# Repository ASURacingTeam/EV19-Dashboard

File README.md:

# ASU Racing Team Formula Students Electric 2019 Dashboard

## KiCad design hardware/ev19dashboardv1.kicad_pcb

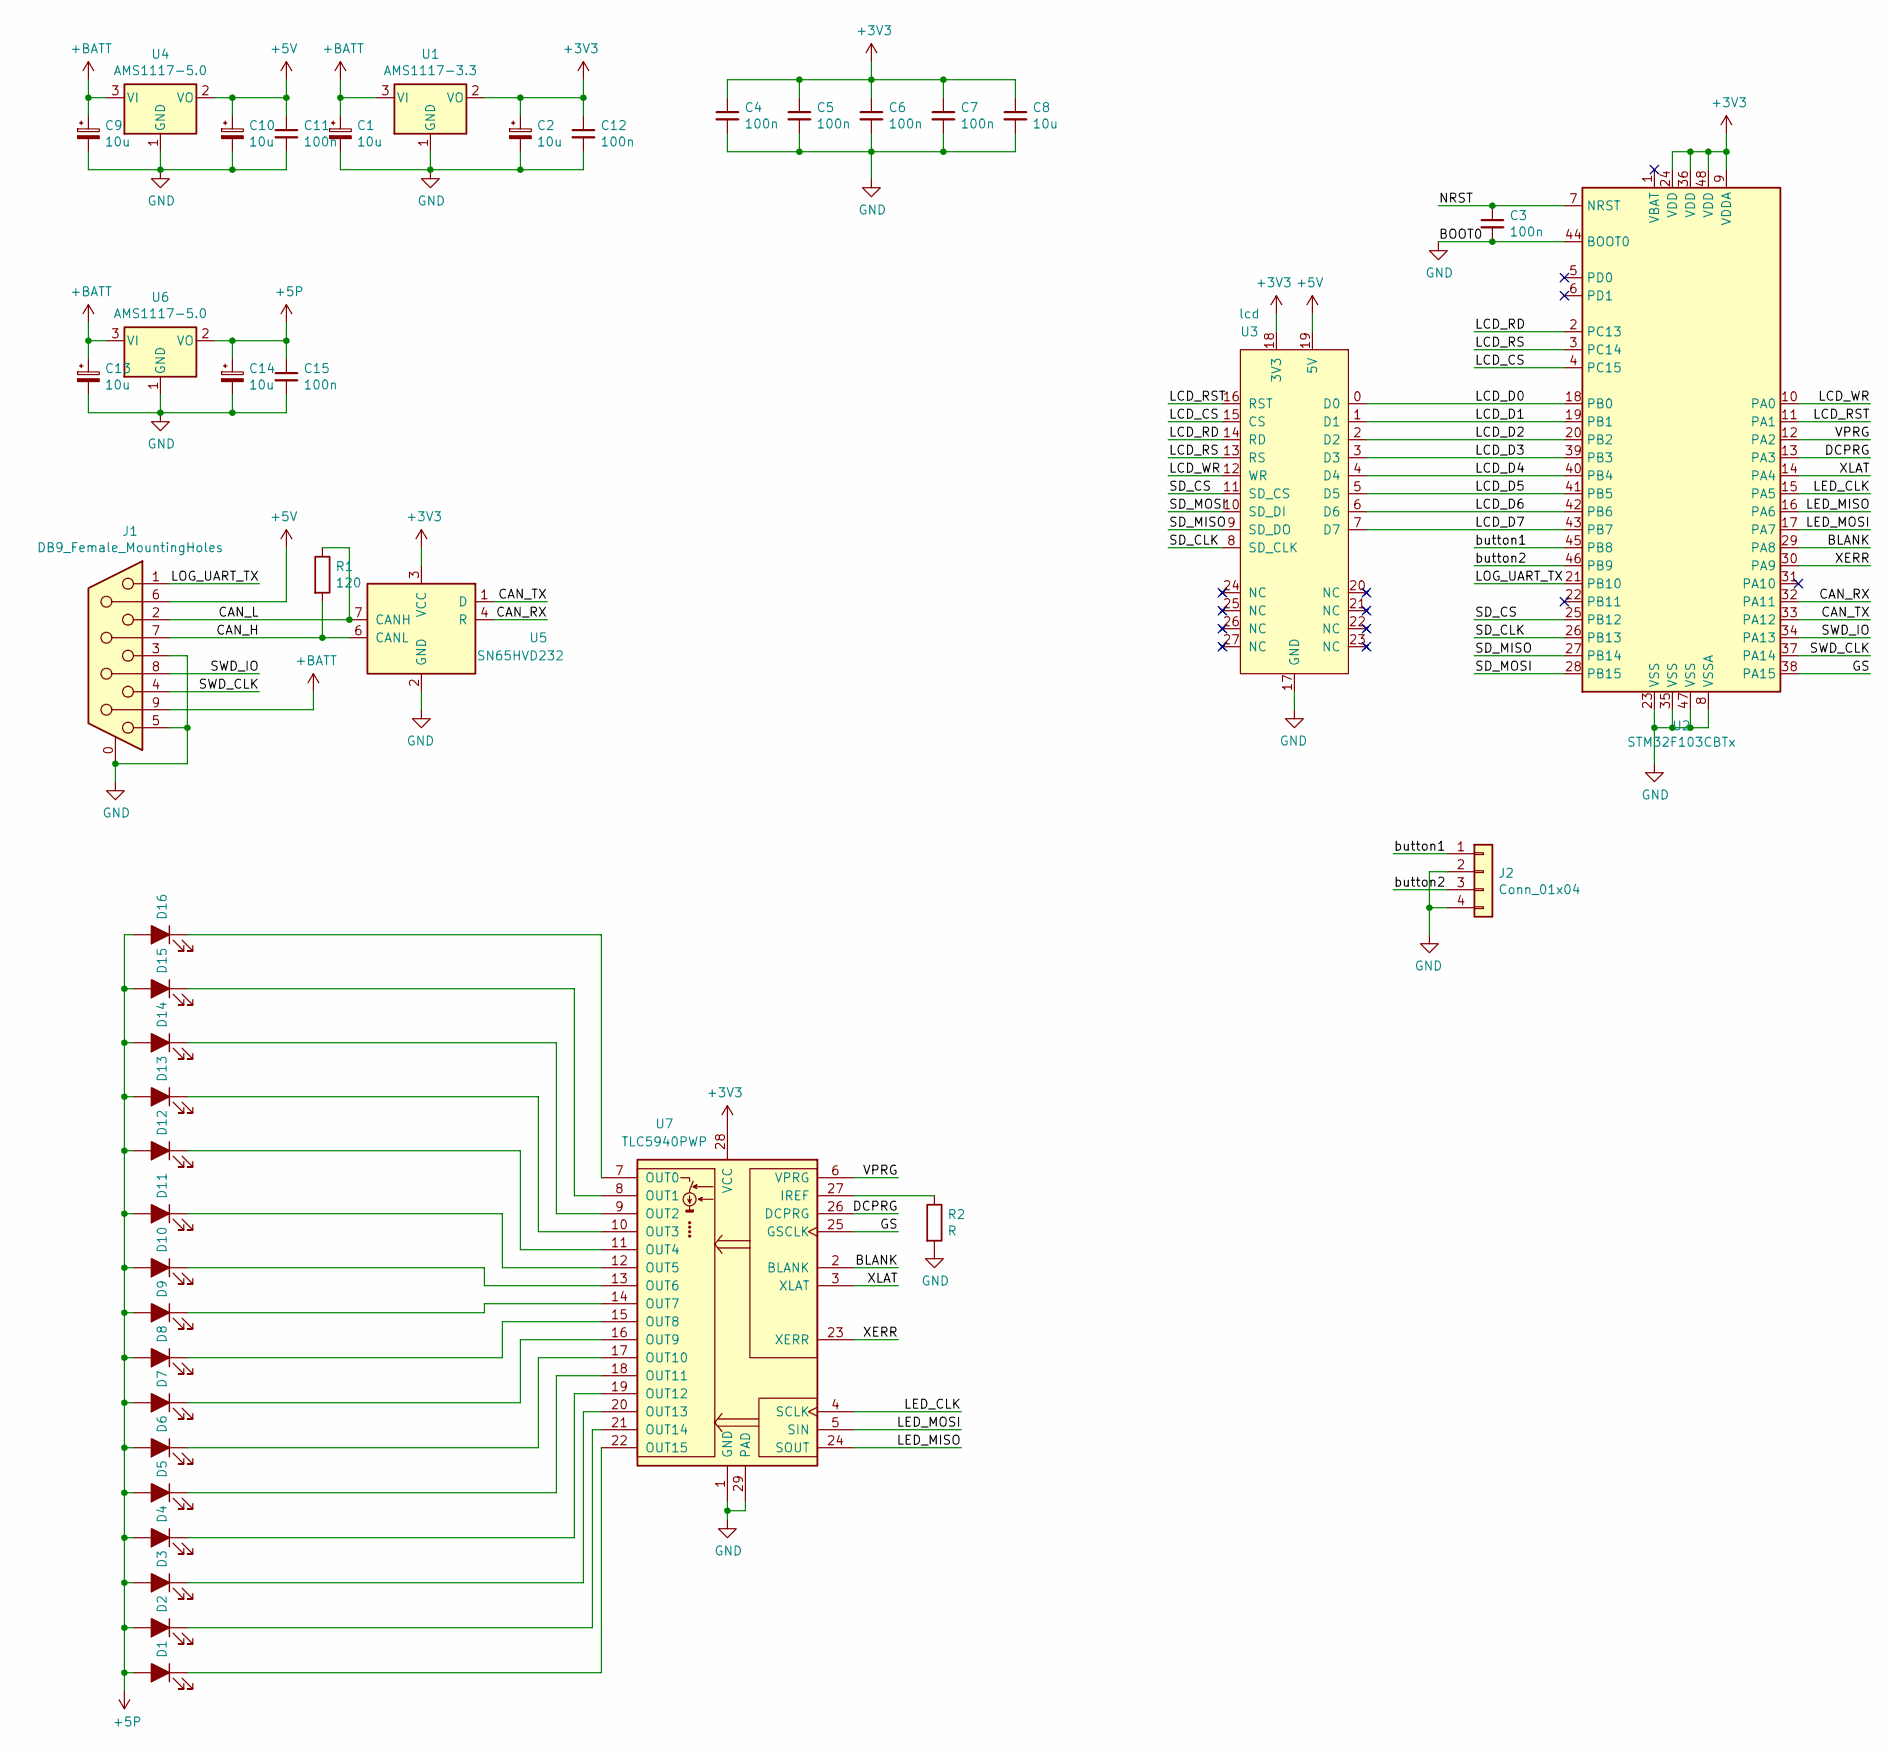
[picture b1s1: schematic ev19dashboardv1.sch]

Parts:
C1, C2, C8, C9, C10, C13, C14: 10u; C_1206_3216Metric_Pad1.42x1.75mm_HandSolder
C3, C4, C5, C6, C7, C11, C12, C15: 100n; C_0805_2012Metric_Pad1.15x1.40mm_HandSolder
D1, D2, D3, D4, D5, D6, D7, D8, D9, D10, D11, D12, D13, D14, D15, D16: LED_ALT; LED_D5.0mm
J1: DB9_Female_MountingHoles; DSUB-9_Female_Vertical_P2.77x2.84mm_MountingHoles
J2: Conn_01x04; PinHeader_1x04_P2.54mm_Vertical
R1: 120; R_0805_2012Metric_Pad1.15x1.40mm_HandSolder
R2: R; R_0805_2012Metric_Pad1.15x1.40mm_HandSolder
U1: AMS1117-3.3; SOT-223-3_TabPin2
U2: STM32F103CBTx; LQFP-48_7x7mm_P0.5mm
U3: lcd; Arduino_35_LCD
U4, U6: AMS1117-5.0; SOT-223-3_TabPin2
U5: SN65HVD232; SOIC-8_3.9x4.9mm_P1.27mm
U7: TLC5940PWP; HTSSOP-28-1EP_4.4x9.7mm_P0.65mm_EP3.4x9.5mm_Mask2.4x6.17mm_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

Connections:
+3V3: C2.1, C4.1, C5.1, C6.1, C7.1, C8.1, C12.1, U1.2 (VO), U2.9 (VDDA), U2.24 (VDD), U2.36 (VDD), U2.48 (VDD), U3.18 (3V3), U5.3 (VCC), U7.28 (VCC)
+5P: C14.1, C15.1, D1.2 (A), D2.2 (A), D3.2 (A), D4.2 (A), D5.2 (A), D6.2 (A), D7.2 (A), D8.2 (A), D9.2 (A), D10.2 (A), D11.2 (A), D12.2 (A), D13.2 (A), D14.2 (A), D15.2 (A), D16.2 (A), U6.2 (VO)
+5V: C10.1, C11.1, J1.6, U3.19 (5V), U4.2 (VO)
+BATT: C1.1, C9.1, C13.1, J1.9, U1.3 (VI), U4.3 (VI), U6.3 (VI)
/BLANK: U2.29 (PA8), U7.2 (BLANK)
/CAN_H: J1.7, R1.2, U5.6 (CANL)
/CAN_L: J1.2, R1.1, U5.7 (CANH)
/CAN_RX: U2.32 (PA11), U5.4 (R)
/CAN_TX: U2.33 (PA12), U5.1 (D)
/DCPRG: U2.13 (PA3), U7.26 (DCPRG)
/GS: U2.38 (PA15), U7.25 (GSCLK)
/LCD_CS: U2.4 (PC15), U3.15 (CS)
/LCD_D0: U2.18 (PB0), U3.0 (D0)
/LCD_D1: U2.19 (PB1), U3.1 (D1)
/LCD_D2: U2.20 (PB2), U3.2 (D2)
/LCD_D3: U2.39 (PB3), U3.3 (D3)
/LCD_D4: U2.40 (PB4), U3.4 (D4)
/LCD_D5: U2.41 (PB5), U3.5 (D5)
/LCD_D6: U2.42 (PB6), U3.6 (D6)
/LCD_D7: U2.43 (PB7), U3.7 (D7)
/LCD_RD: U2.2 (PC13), U3.14 (RD)
/LCD_RS: U2.3 (PC14), U3.13 (RS)
/LCD_RST: U2.11 (PA1), U3.16 (RST)
/LCD_WR: U2.10 (PA0), U3.12 (WR)
/LED_CLK: U2.15 (PA5), U7.4 (SCLK)
/LED_MISO: U2.16 (PA6), U7.24 (SOUT)
/LED_MOSI: U2.17 (PA7), U7.5 (SIN)
/LOG_UART_TX: J1.1, U2.21 (PB10)
/NRST: C3.1, U2.7 (NRST)
/SD_CLK: U2.26 (PB13), U3.8 (SD_CLK)
/SD_CS: U2.25 (PB12), U3.11 (SD_CS)
/SD_MISO: U2.27 (PB14), U3.9 (SD_DO)
/SD_MOSI: U2.28 (PB15), U3.10 (SD_DI)
/SWD_CLK: J1.4, U2.37 (PA14)
/SWD_IO: J1.8, U2.34 (PA13)
/VPRG: U2.12 (PA2), U7.6 (VPRG)
/XERR: U2.30 (PA9), U7.23 (XERR)
/XLAT: U2.14 (PA4), U7.3 (XLAT)
/button1: J2.1, U2.45 (PB8)
/button2: J2.3, U2.46 (PB9)
GND: C1.2, C2.2, C3.2, C4.2, C5.2, C6.2, C7.2, C8.2, C9.2, C10.2, C11.2, C12.2, C13.2, C14.2, C15.2, J1.0 (PAD), J1.3, J1.5, J2.2, J2.4, R2.2, U1.1 (GND), U2.8 (VSSA), U2.23 (VSS), U2.35 (VSS), U2.44 (BOOT0), U2.47 (VSS), U3.17 (GND), U4.1 (GND), U5.2 (GND), U6.1 (GND), U7.1 (GND), U7.29 (PAD)
unnamed: D1.1 (K), U7.22 (OUT15)
unnamed: D2.1 (K), U7.21 (OUT14)
unnamed: D3.1 (K), U7.20 (OUT13)
unnamed: D4.1 (K), U7.19 (OUT12)
unnamed: D5.1 (K), U7.18 (OUT11)
unnamed: D6.1 (K), U7.17 (OUT10)
unnamed: D7.1 (K), U7.16 (OUT9)
unnamed: D8.1 (K), U7.15 (OUT8)
unnamed: D9.1 (K), U7.14 (OUT7)
unnamed: D10.1 (K), U7.13 (OUT6)
unnamed: D11.1 (K), U7.12 (OUT5)
unnamed: D12.1 (K), U7.11 (OUT4)
unnamed: D13.1 (K), U7.10 (OUT3)
unnamed: D14.1 (K), U7.9 (OUT2)
unnamed: D15.1 (K), U7.8 (OUT1)
unnamed: D16.1 (K), U7.7 (OUT0)
unnamed: R2.1, U7.27 (IREF)

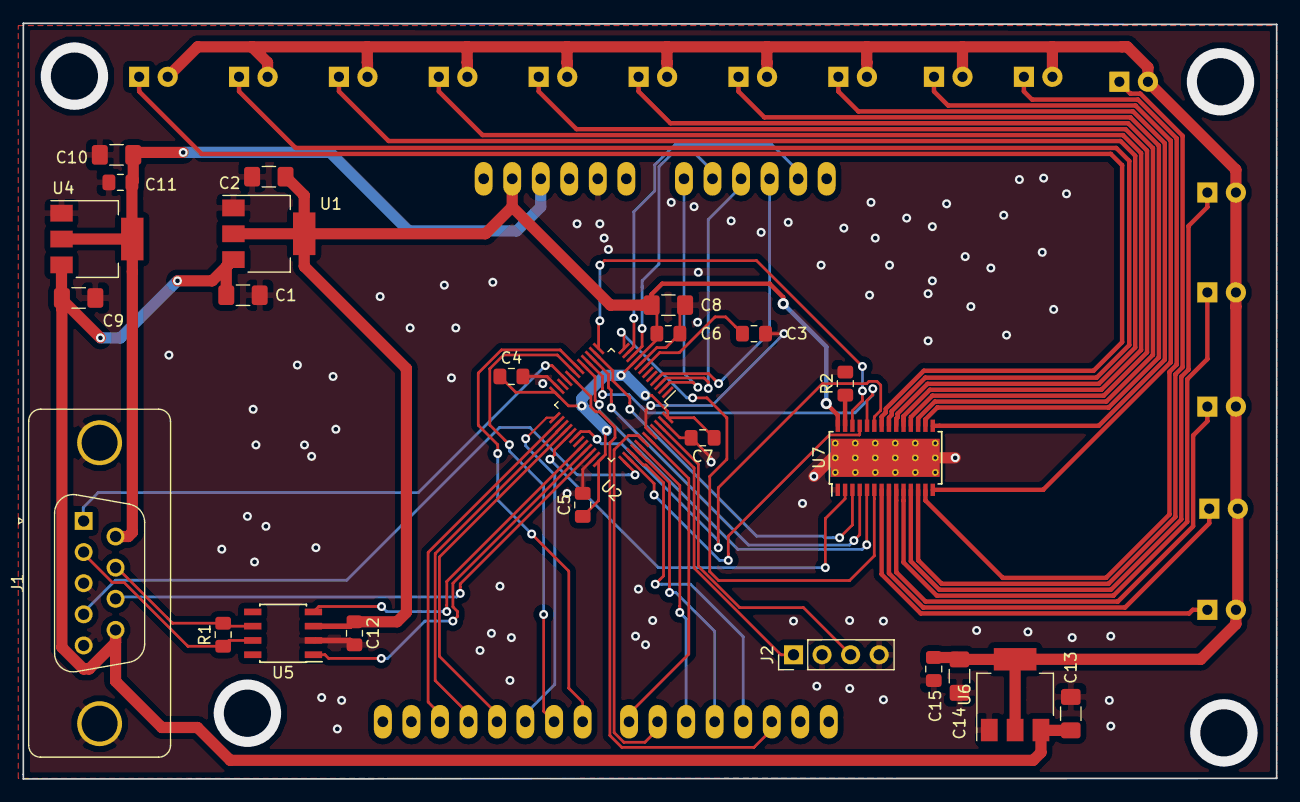
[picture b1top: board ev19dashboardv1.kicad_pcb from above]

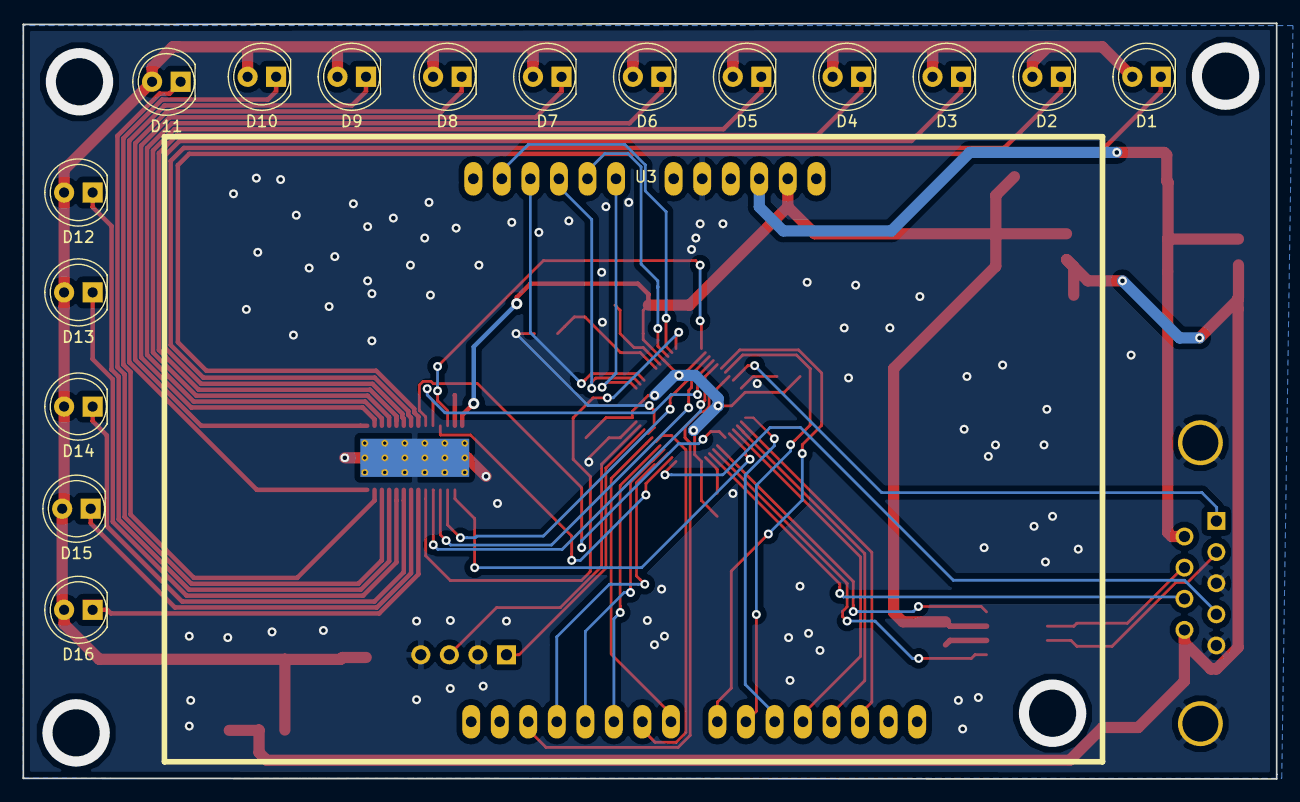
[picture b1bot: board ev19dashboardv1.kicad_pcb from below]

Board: 2 copper layers, 111.5 x 67.2 mm, 42 parts (17 on the bottom side), 58 nets.

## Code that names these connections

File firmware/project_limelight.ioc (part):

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Mcu.Name=STM32F103C(8-B)Tx
Mcu.Package=LQFP48
Mcu.UserName=STM32F103CBTx
PA0-WKUP.GPIOParameters=GPIO_Label
PA0-WKUP.GPIO_Label=LCD_WR
PA0-WKUP.Signal=GPIO_Output
PA1.GPIOParameters=GPIO_Label
PA1.GPIO_Label=LCD_RST
PA1.Signal=GPIO_Output
PA11.Mode=Master
PA11.Signal=CAN_RX
PA12.Mode=Master
PA12.Signal=CAN_TX
PA13.GPIOParameters=GPIO_Label
PA13.GPIO_Label=SWDIO
PA13.Mode=Serial_Wire
PA13.Signal=SYS_JTMS-SWDIO
PA14.GPIOParameters=GPIO_Label
PA14.GPIO_Label=SWCLK
PA14.Mode=Serial_Wire
PA14.Signal=SYS_JTCK-SWCLK
PA15.GPIOParameters=GPIO_Label
PA15.GPIO_Label=LED_GS
PA15.Signal=S_TIM2_CH1_ETR
PA2.GPIOParameters=GPIO_Label
PA2.GPIO_Label=LED_VPRG
PA2.Signal=GPIO_Output
PA3.GPIOParameters=GPIO_Label
PA3.GPIO_Label=LED_DCPRG
PA3.Signal=GPIO_Output
PA4.GPIOParameters=GPIO_Label
PA4.GPIO_Label=LED_XLAT
PA4.Signal=GPIO_Output
PA5.GPIOParameters=GPIO_Label
PA5.GPIO_Label=LED_CLK
PA5.Mode=Full_Duplex_Master
PA5.Signal=SPI1_SCK
PA6.GPIOParameters=GPIO_Label
PA6.GPIO_Label=LED_MISO
PA6.Mode=Full_Duplex_Master
PA6.Signal=SPI1_MISO
PA7.GPIOParameters=GPIO_Label
PA7.GPIO_Label=LED_MOSI
PA7.Mode=Full_Duplex_Master
PA7.Signal=SPI1_MOSI
PA8.GPIOParameters=PinState,GPIO_Label
PA8.GPIO_Label=LED_BLANK
PA8.PinState=GPIO_PIN_SET
PA8.Signal=GPIO_Output
PA9.GPIOParameters=GPIO_Label
PA9.GPIO_Label=LED_XERR
PA9.Signal=GPIO_Input
PB0.GPIOParameters=GPIO_Speed,PinState,GPIO_Label
PB0.GPIO_Label=LCD_D0
PB0.GPIO_Speed=GPIO_SPEED_FREQ_HIGH
PB0.PinState=GPIO_PIN_RESET
PB0.Signal=GPIO_Output
PB1.GPIOParameters=GPIO_Speed,GPIO_Label
PB1.GPIO_Label=LCD_D1
PB1.GPIO_Speed=GPIO_SPEED_FREQ_HIGH
PB1.Signal=GPIO_Output
PB10.GPIOParameters=GPIO_Label
PB10.GPIO_Label=LOG_UART_TX
PB10.Mode=Asynchronous
PB10.Signal=USART3_TX
PB11.GPIOParameters=GPIO_Label
PB11.GPIO_Label=UNUSED
PB11.Mode=Asynchronous
PB11.Signal=USART3_RX
PB12.GPIOParameters=GPIO_Label
PB12.GPIO_Label=SD_CS
PB12.Signal=GPIO_Output
PB13.GPIOParameters=GPIO_Label
PB13.GPIO_Label=SD_CLK
PB13.Mode=Full_Duplex_Master
PB13.Signal=SPI2_SCK
PB14.GPIOParameters=GPIO_PuPd,GPIO_Label
PB14.GPIO_Label=SD_MISO
PB14.GPIO_PuPd=GPIO_PULLUP
PB14.Mode=Full_Duplex_Master
PB14.Signal=SPI2_MISO
PB15.GPIOParameters=GPIO_Label
PB15.GPIO_Label=SD_MOSI
PB15.Mode=Full_Duplex_Master
PB15.Signal=SPI2_MOSI
PB2.GPIOParameters=GPIO_Speed,GPIO_Label
PB2.GPIO_Label=LCD_D2
PB2.GPIO_Speed=GPIO_SPEED_FREQ_HIGH
PB2.Signal=GPIO_Output
PB3.GPIOParameters=GPIO_Speed,GPIO_Label
PB3.GPIO_Label=LCD_D3
PB3.GPIO_Speed=GPIO_SPEED_FREQ_HIGH
PB3.Signal=GPIO_Output
PB4.GPIOParameters=GPIO_Speed,GPIO_Label
PB4.GPIO_Label=LCD_D4
PB4.GPIO_Speed=GPIO_SPEED_FREQ_HIGH
PB4.Signal=GPIO_Output
PB5.GPIOParameters=GPIO_Speed,GPIO_Label
PB5.GPIO_Label=LCD_D5
PB5.GPIO_Speed=GPIO_SPEED_FREQ_HIGH
PB5.Signal=GPIO_Output
PB6.GPIOParameters=GPIO_Speed,GPIO_Label
PB6.GPIO_Label=LCD_D6
PB6.GPIO_Speed=GPIO_SPEED_FREQ_HIGH
PB6.Signal=GPIO_Output
PB7.GPIOParameters=GPIO_Speed,GPIO_Label
PB7.GPIO_Label=LCD_D7
PB7.GPIO_Speed=GPIO_SPEED_FREQ_HIGH
PB7.Signal=GPIO_Output
PC13-TAMPER-RTC.GPIOParameters=GPIO_Label
PC13-TAMPER-RTC.GPIO_Label=LCD_RD
PC13-TAMPER-RTC.Signal=GPIO_Output
PC14-OSC32_IN.GPIOParameters=GPIO_Label
PC14-OSC32_IN.GPIO_Label=LCD_RS
PC14-OSC32_IN.Signal=GPIO_Output
PC15-OSC32_OUT.GPIOParameters=GPIO_Label
PC15-OSC32_OUT.GPIO_Label=LCD_CS
PC15-OSC32_OUT.Signal=GPIO_Output
RCC.SYSCLKFreq_VALUE=64000000
RCC.SYSCLKSource=RCC_SYSCLKSOURCE_PLLCLK
board=custom

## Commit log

2019-08-30 added firmware and hardware
